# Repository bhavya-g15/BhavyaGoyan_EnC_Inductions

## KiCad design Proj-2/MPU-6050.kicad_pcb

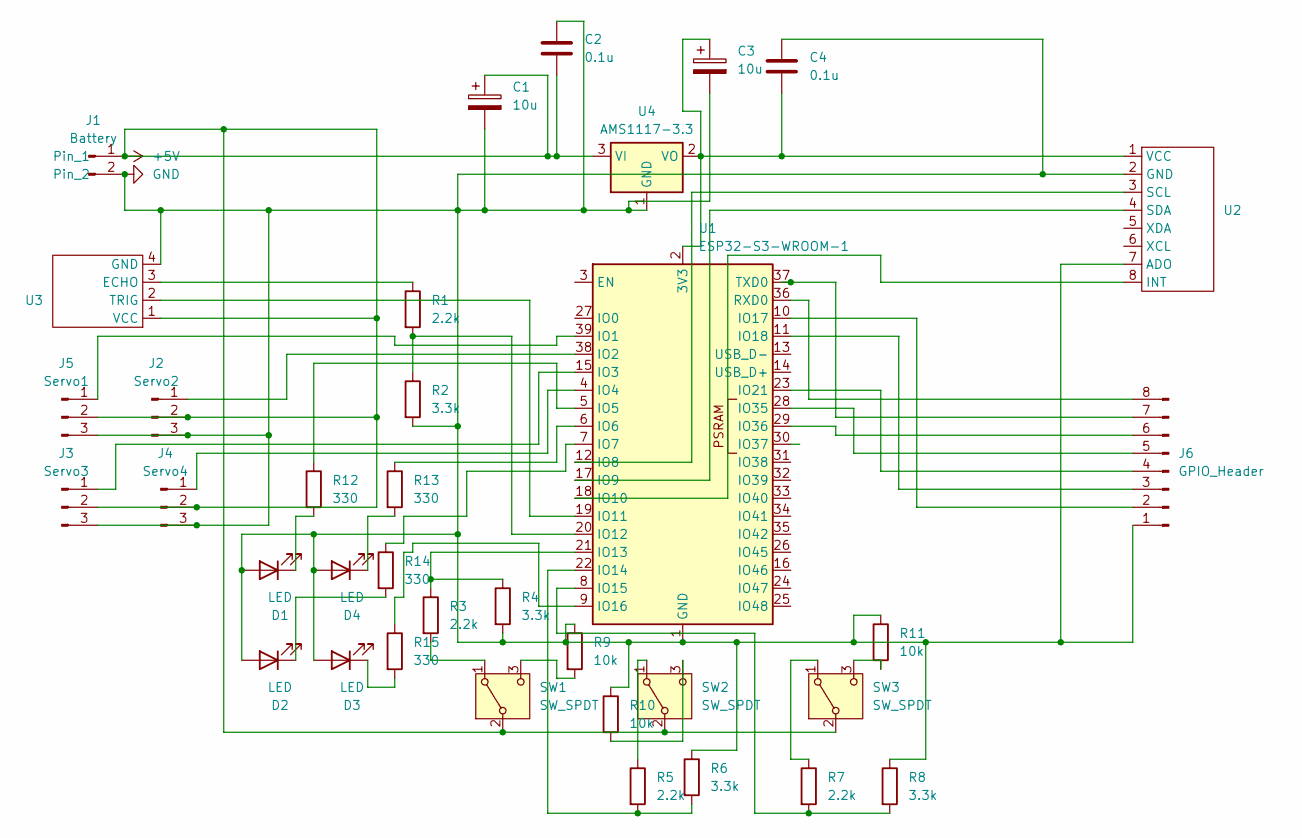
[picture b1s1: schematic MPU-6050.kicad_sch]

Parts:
C1, C3: 10u; C_0805_2012Metric
C2, C4: 0.1u; C_0805_2012Metric
D1, D2, D3, D4: LED; LED_0805_2012Metric
J1: Battery; PinHeader_1x02_P2.54mm_Vertical_SMD_Pin1Right
J2: Servo2; PinHeader_1x03_P2.54mm_Vertical_SMD_Pin1Right
J3: Servo3; PinHeader_1x03_P2.54mm_Vertical_SMD_Pin1Right
J4: Servo4; PinHeader_1x03_P2.54mm_Vertical_SMD_Pin1Right
J5: Servo1; PinHeader_1x03_P2.54mm_Vertical_SMD_Pin1Right
J6: GPIO_Header; PinHeader_1x08_P2.54mm_Vertical_SMD_Pin1Right
R1, R3, R5, R7: 2.2k; R_0805_2012Metric
R2, R4, R6, R8: 3.3k; R_0805_2012Metric
R9, R10, R11: 10k; R_0805_2012Metric
R12, R13, R14, R15: 330; R_0805_2012Metric
SW1, SW2, SW3: SW_SPDT; PinHeader_1x03_P2.54mm_Vertical_SMD_Pin1Right
U1: ESP32-S3-WROOM-1
U2: MPU-6050
U3: HC-SR04
U4: AMS1117-3.3; SOT-223-3_TabPin2

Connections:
+5V: C1.1, C2.2, J1.1, J2.2, J3.2, J4.2, J5.2, SW1.2 (B), SW2.2 (B), SW3.2 (B), U3.1 (VCC), U4.3 (VI)
GND: C1.2, C2.1, C3.2, C4.1, D1.2 (A), D2.2 (A), D3.2 (A), D4.2 (A), J1.2, J2.3, J3.3, J4.3, J5.3, J6.1, R2.2, R4.2, R6.1, R8.1, R9.1, R10.1, R11.1, U1.1 (GND), U1.40 (GND), U1.41 (GND), U2.2 (GND), U2.7 (ADO), U3.4 (GND), U4.1 (GND)
unnamed: D1.1 (K), R12.2
unnamed: D2.1 (K), R14.2
unnamed: D3.1 (K), R15.2
unnamed: D4.1 (K), R13.2
unnamed: J2.1, U1.38 (IO2)
unnamed: J3.1, U1.15 (IO3)
unnamed: J4.1, U1.4 (IO4)
unnamed: J5.1, U1.39 (IO1)
unnamed: J6.2, U1.10 (IO17)
unnamed: J6.3, U1.11 (IO18)
unnamed: J6.4, U1.23 (IO21)
unnamed: J6.5, U1.28 (IO35)
unnamed: J6.6, U1.29 (IO36)
unnamed: J6.7, U1.37 (TXD0)
unnamed: J6.8, U1.36 (RXD0)
unnamed: R3.2, SW1.1 (A)
unnamed: R9.2, SW1.3 (C)
unnamed: R5.1, SW2.1 (A)
unnamed: R10.2, SW2.3 (C)
unnamed: R7.1, SW3.1 (A)
unnamed: R11.2, SW3.3 (C)
unnamed: C3.1, C4.2, U1.2 (3V3), U2.1 (VCC), U4.2 (VO)
unnamed: R12.1, U1.5 (IO5)
unnamed: R13.1, U1.6 (IO6)
unnamed: R14.1, U1.7 (IO7)
unnamed: U1.12 (IO8), U2.3 (SCL)
unnamed: U1.17 (IO9), U2.4 (SDA)
unnamed: U1.18 (IO10), U2.8 (INT)
unnamed: U1.19 (IO11), U3.2 (TRIG)
unnamed: R1.2, R2.1, U1.20 (IO12)
unnamed: R3.1, R4.1, U1.21 (IO13)
unnamed: R5.2, R6.2, U1.22 (IO14)
unnamed: R7.2, R8.2, U1.8 (IO15)
unnamed: R15.1, U1.9 (IO16)
unnamed: R1.1, U3.3 (ECHO)

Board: 2 copper layers, 36 parts (0 on the bottom side), 37 nets, no tracks yet.

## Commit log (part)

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2026-06-28 PCB Projects
2026-06-29 Create Proj-1
2026-06-29 Create Proj-2
2026-06-29 Create libs
